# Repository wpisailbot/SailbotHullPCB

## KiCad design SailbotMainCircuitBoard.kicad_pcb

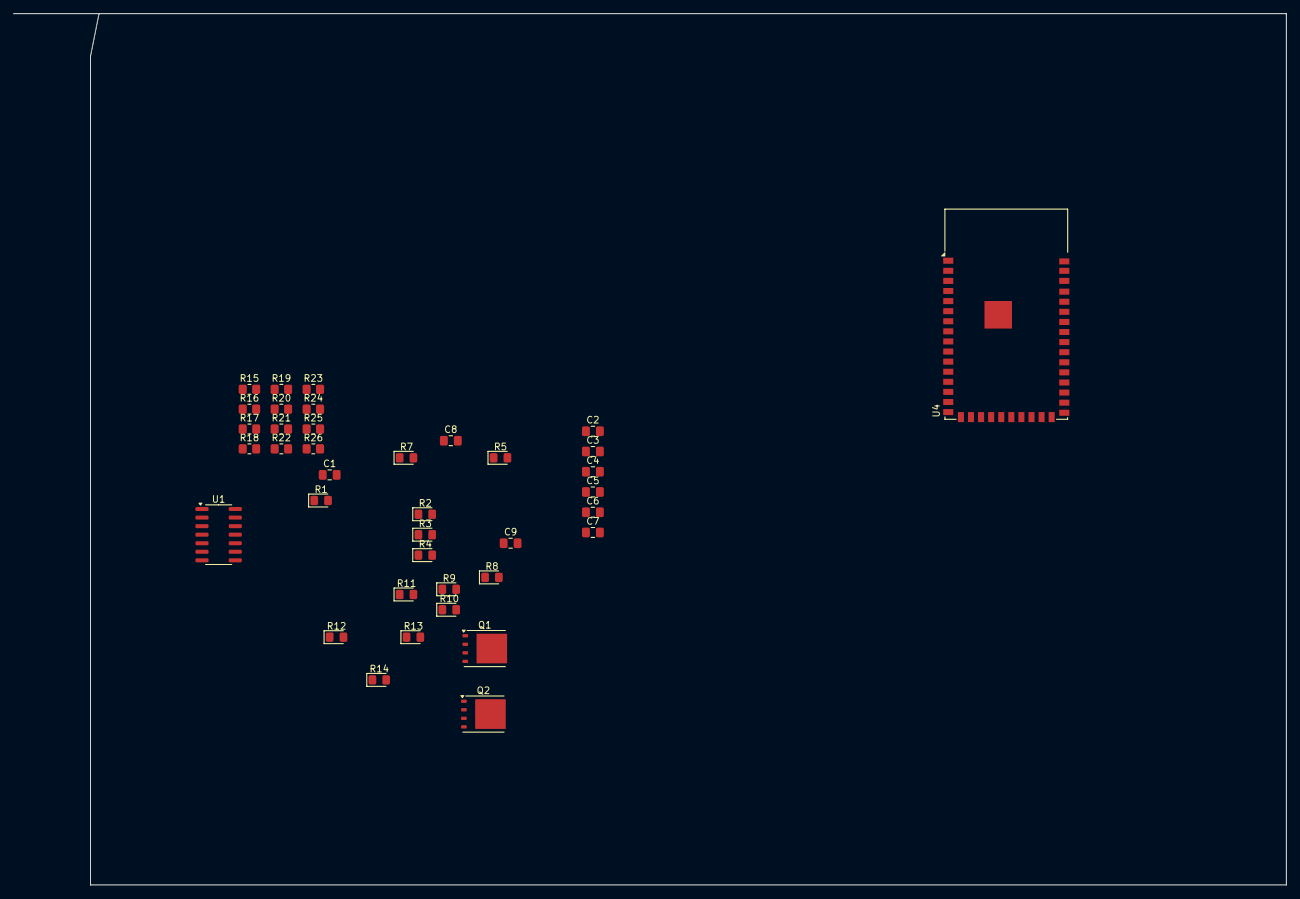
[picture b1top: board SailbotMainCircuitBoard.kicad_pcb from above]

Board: 2 copper layers, 189.2 x 129.5 mm, 38 parts (0 on the bottom side), 28 nets, no tracks yet.

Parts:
C1, C2, C3, C4, C7, C8, C9: 0.1uF; C_0805_2012Metric_Pad1.18x1.45mm_HandSolder
C5, C6: 1uF; C_0805_2012Metric_Pad1.18x1.45mm_HandSolder
Q1, Q2: CSD18534Q5A; TDSON-8-1
R1, R2, R3, R4, R5: 1k; LED_0805_2012Metric_Pad1.15x1.40mm_HandSolder
R7, R8: 100; LED_0805_2012Metric_Pad1.15x1.40mm_HandSolder
R9: 10k; LED_0805_2012Metric_Pad1.15x1.40mm_HandSolder
R10, R12: 5.1k; LED_0805_2012Metric_Pad1.15x1.40mm_HandSolder
R11, R13: 10M; LED_0805_2012Metric_Pad1.15x1.40mm_HandSolder
R14: 450k; LED_0805_2012Metric_Pad1.15x1.40mm_HandSolder
R15, R16, R17, R18, R19, R20, R21, R22, R23, R24, R25, R26: 1k; R_0805_2012Metric_Pad1.20x1.40mm_HandSolder
U1: OPA4197xD; SOIC-14_3.9x8.7mm_P1.27mm
U4: ESP32-S2-WROVER

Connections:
GND: Q2.1 (S), Q2.2 (S), Q2.3 (S), R13.2, R14.2, R21.1, R22.1, R23.1, U1.11 (V-)
GNDREF: C1.2, C2.2, C3.2, C4.2, C5.2, C6.1, C7.1, C9.2, R7.2
unnamed: C8.2, C9.1, R8.1
unnamed: C7.2, C8.1, R7.1
unnamed: C1.1, R1.2
unnamed: C2.1, R2.2
unnamed: C3.1, R3.2
unnamed: C4.1, R5.2
unnamed: C5.1, R4.2
unnamed: Q1.5 (D), Q2.5 (D)
unnamed: Q1.4 (G), R10.2, R11.1
unnamed: Q1.1 (S), Q1.2 (S), Q1.3 (S), R8.2, R11.2
unnamed: Q2.4 (G), R12.2, R13.1
unnamed: R15.1, U1.1, U1.2 (-)
unnamed: R16.1, R18.1, U1.6 (-), U1.7
unnamed: R17.1, R19.1, U1.8, U1.9 (-)
unnamed: R20.1, U1.13 (-), U1.14
unnamed: R15.2, R21.2
unnamed: R18.2, R24.1
unnamed: R16.2, R22.2
unnamed: R19.2, R25.1
unnamed: R17.2, R23.2
unnamed: R20.2, R26.1
unnamed: U4.1 (GND), U4.26 (GND), U4.42 (GND), U4.43 (GND)
V1: R4.1, R5.1, U1.3 (+), U1.4 (V+)
V2: R3.1, U1.5 (+)
V3: R2.1, U1.10 (+)
V4: R1.1, U1.12 (+)

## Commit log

2024-11-21 Initial commit + rough BMS circuit redo
2024-11-21 Added 2024 Hull PCB from Altium Designer
2025-01-27 Added ADC Circuit schetch to read individual cell voltages
2025-10-05 Pushing updated schematics
